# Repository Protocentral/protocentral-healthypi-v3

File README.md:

# ProtoCentral HealthyPi v3 HAT for Raspberry Pi

HealthyPi is the first fully open-source, full-featured vital sign monitor. Using the Raspberry Pi as its computing and display platform, the HealthyPi add-on HAT turns the Raspberry Pi into a vital sign monitoring system.

If you don't already have one, you can now buy HealthyPi from any of the following places:

* [Crowd Supply](https://www.crowdsupply.com/protocentral/healthypi-v3)
* [ProtoCentral India (Worldwide)](https://www.protocentral.com/open-source-health/1252-healthypi-v3-complete-kit-includes-raspberry-pi.html)
* [DigiKey](https://www.digikey.in/product-detail/en/crowd-supply-inc/CS-HEALTHYPI-01/1848-1035-ND)
* [Mouser](https://www.mouser.in/ProductDetail/392-CS-HEALTHYPI-01)

Repository Contents
-------------------
* **/firmware** - Atmel studio  and aduino example sketches.
* **/Hardware** - All Eagle design files (.brd, .sch)
* **/extras** - includes the datasheet
* **/gui** - HealthyPi GUI for Raspberry Pi and PC
* **/docs** - Documentation

Getting Started (On Raspberry Pi):
----------------------------------

### For getting started videos and tutorials, please go to [http://healthypi.protocentral.com](http://healthypi.protocentral.com)

Mount ProtoCentral's HealthyPi-v3 HAT carefully onto the Raspberry Pi Board's GPIO Pins. Connect this setup with the Raspberry Pi's Display or a HDMI Monitor. The HAT communicates with Raspberry Pi using UART interface on the GPIO pin header. Connect the ECG electrodes and SPO2 Probe to the ProtoCentral's Healthy PI Hat.

It's now easy to get started with our brand-new installation script. Just follow the following steps on your Raspberry Pi.

To start, open up the terminal window (Menu -> Accessories -> Terminal) on Raspbian running on your Raspberry Pi:

In the terminal window, type the following lines.

```bash
curl -sS http://pi.protocentral.com/hpi3.sh | sudo bash
```

It really is as simple as that !!

This code will install all the required overlays, configuration and application files to get the Healthy Pi up and running.

After the script reboots, you should be able to see the GUI display on the screen

### This completes the install!

If the above script does not work for you and would like to do a manual installation or would like to customize the code, check out [Advanced HealthyPi] (/docs/advanced-healthypi.md).

Using the HealthyPi GUI on Windows, MacOS and Linux
---------------------------------------------------
The HealthyPi board now streams the same data on the on-board USB port. This allows you to get the same data that goes to the Raspberry Pi, now on your desktop PC as well.

Java 8 is required on all platforms for running the processing-based GUI application. You can download Java for your platform from the following link.

[https://java.com/en/download/](https://java.com/en/download/)

#### Installing drivers (only for Windows)

HealthyPi uses the same drivers as an Arduino Zero. Once plugged in to the USB port, the device would be recognized as an "Unknown Device". You can locate the device is the Windows Device Manager and manually install the drivers provided in the "drivers" folder in the Windows Executable ZIP archive provided.

MacOS and Linux do not need any drivers to be installed.

### Processing GUI Installation

Download the zip file containing the executable files from the releases section for 32-bit/64-bit Windows. If you do not know if you have a 64-bit or 32-bit computer, please download the 32-bit version.

[Download the latest GUI for HealthyPi](https://github.com/Protocentral/protocentral-healthypi-v3/releases/latest)

Simply download the appropriate file for your operating system, unzip the contents and run the executable program contained in it.

### For more documentation, videos and tutorials, please go to [http://healthypi.protocentral.com](http://healthypi.protocentral.com)

License Information
===================

This product is open source! Both, our hardware and software are open source and licensed under the following licenses:

Hardware
---------

**All hardware is released under [Creative Commons Share-alike 4.0 International](http://creativecommons.org/licenses/by-sa/4.0/).**

You are free to:

* Share — copy and redistribute the material in any medium or format
* Adapt — remix, transform, and build upon the material for any purpose, even commercially.
The licensor cannot revoke these freedoms as long as you follow the license terms.

Under the following terms:

* Attribution — You must give appropriate credit, provide a link to the license, and indicate if changes were made. You may do so in any reasonable manner, but not in any way that suggests the licensor endorses you or your use.
* ShareAlike — If you remix, transform, or build upon the material, you must distribute your contributions under the same license as the original.

Software
--------

**All software is released under the MIT License(http://opensource.org/licenses/MIT).**

THE SOFTWARE IS PROVIDED "AS IS", WITHOUT WARRANTY OF ANY KIND, EXPRESS OR IMPLIED, INCLUDING BUT NOT LIMITED TO THE WARRANTIES OF MERCHANTABILITY, FITNESS FOR A PARTICULAR PURPOSE AND NONINFRINGEMENT. IN NO EVENT SHALL THE AUTHORS OR COPYRIGHT HOLDERS BE LIABLE FOR ANY CLAIM, DAMAGES OR OTHER LIABILITY, WHETHER IN AN ACTION OF CONTRACT, TORT OR OTHERWISE, ARISING FROM, OUT OF OR IN CONNECTION WITH THE SOFTWARE OR THE USE OR OTHER DEALINGS IN THE SOFTWARE.

Please check [*LICENSE.md*](LICENSE.md) for detailed license descriptions.

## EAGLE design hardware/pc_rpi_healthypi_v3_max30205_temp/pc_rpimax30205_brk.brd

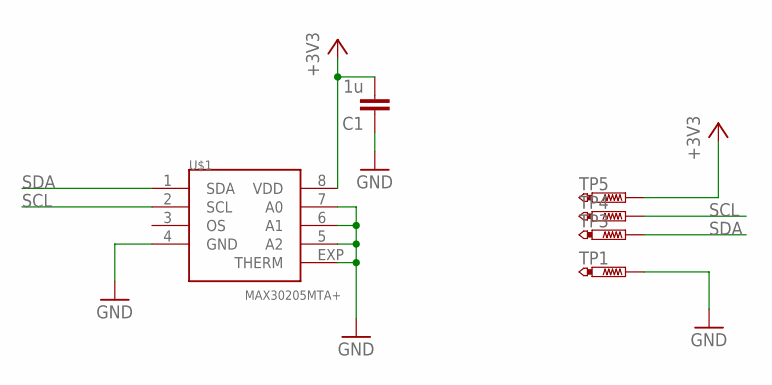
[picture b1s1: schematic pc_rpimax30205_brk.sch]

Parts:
C1: 1u; C0805
TP1, TP3, TP4, TP5: PTR1TP20SQ; TP20SQ
U$1: MAX30205MTA+; TDFN-08

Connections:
+3V3: C1.2, TP5.TP, U$1.8 (VDD)
GND: C1.1, TP1.TP, U$1.4 (GND), U$1.5 (A2), U$1.6 (A1), U$1.7 (A0), U$1.EXP (THERM)
SCL: TP4.TP, U$1.2 (SCL)
SDA: TP3.TP, U$1.1 (SDA)

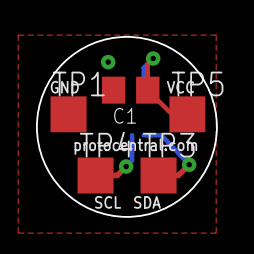
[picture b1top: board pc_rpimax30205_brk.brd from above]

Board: 4 copper layers, 10.0 x 10.0 mm, 6 parts (1 on the bottom side), 4 nets.

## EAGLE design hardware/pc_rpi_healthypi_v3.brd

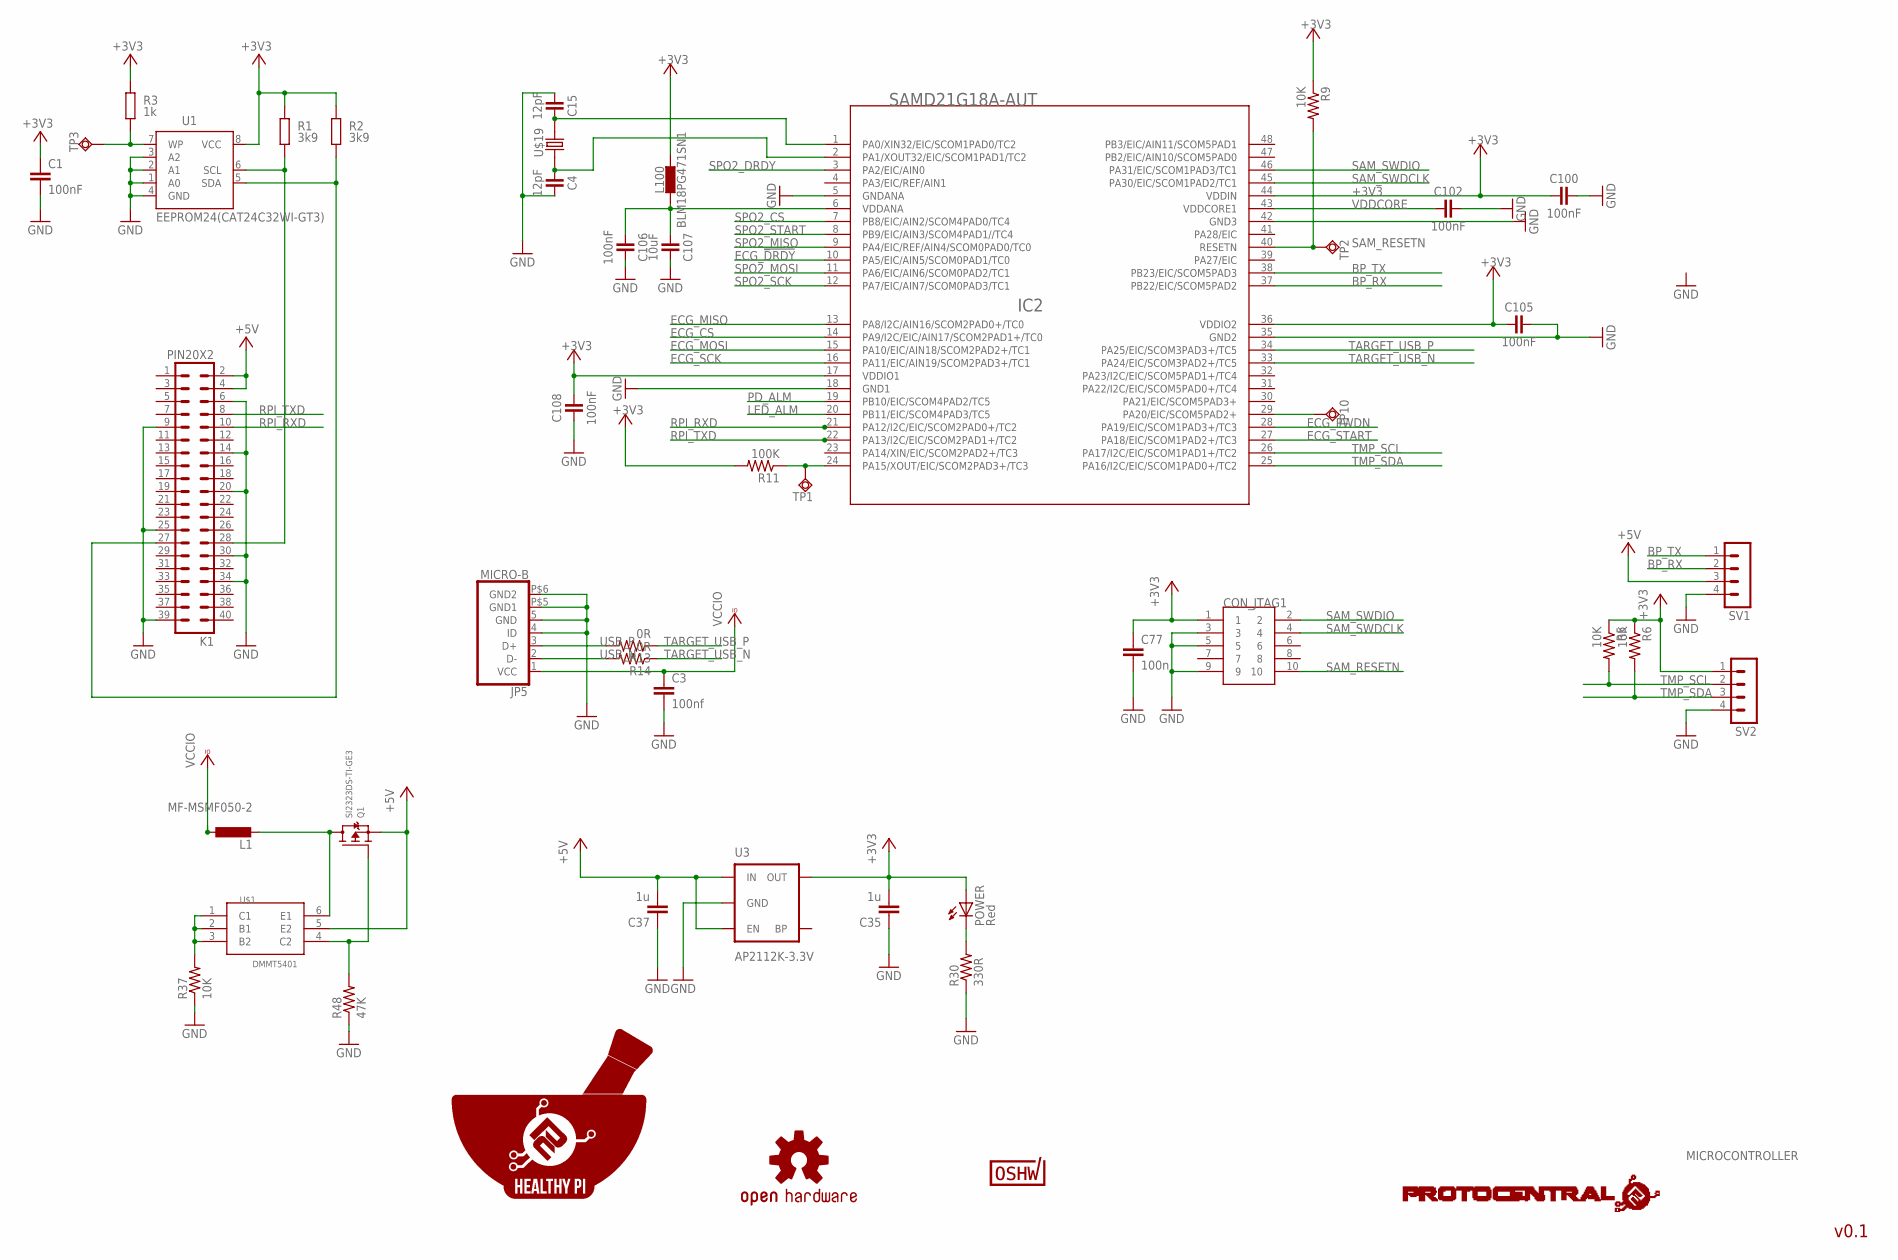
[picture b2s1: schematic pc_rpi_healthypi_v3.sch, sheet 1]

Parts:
C1: 100nF; C0805K
C3: 100nf; C0402
C4, C15: 12pF; C0402
C35, C37: 1u; C0402
C77: 100n; C0805
C100, C102, C105, C106, C108: 100nF; C0805
C107: 10uF; C0805
CON_JTAG1: HDR-SMT-50MIL/5X2(20021121-00010C4LF); HDR-SMT-50MIL/5X2
IC2: SAMD21G18A-AUT; TQFP48
JP5: MICRO-B
K1: PIN20X2; PIN_20X2
L1: MF-MSMF050-2; L1812
L100: BLM18PG471SN1; C0603
POWER: Red; CHIPLED_0603
Q1: SI2323DS-TI-GE3; SOT23-R
R1, R2: 3k9; M0805; TOLERANCE 5%
R3: 1k; M0805; TOLERANCE 5%
R5, R6: 10K; R0402
R9, R37: 10K; R0805
R11: 100K; R0805
R13, R14: 0R; R0402
R30: 330R; R0402
R48: 47K; R0805
SV1, SV2: MA04-1
TP1, TP2, TP3, TP10: TPSQB1,27; B1,27
U1: EEPROM24(CAT24C32WI-GT3); SOIC8
U3: AP2112K-3.3V; SOT23-5
U$1: DMMT5401; SOT26
U$5: OSHW-LOGOM; OSHW-LOGO-M
U$6: PROTY_LOGO_WITH_TEXT; PROTY_WITH_TEXT
U$13: CERT-SMALL; CERT-SMALL-SILK
U$15: HEALTHYPI
U$19: 520-327-12.5-34B(32.768KHZ); ECX-31B

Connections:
+3V3: C1.1, C35.2, C77.1, C100.1, C105.1, C108.2, CON_JTAG1.1, IC2.17 (VDDIO1), IC2.36 (VDDIO2), IC2.44 (VDDIN), L100.2, POWER.A, R1.2, R2.2, R3.2, R5.1, R6.1, R9.1, R11.2, SV2.1, U1.8 (VCC), U3.5 (OUT); also elsewhere on the board
+5V: C37.2, K1.2, K1.4, Q1.2 (S), SV1.3, U3.1 (IN), U3.3 (EN), U$1.5 (E2)
BP_RX: IC2.37 (PB22/EIC/SCOM5PAD2), SV1.2
BP_TX: IC2.38 (PB23/EIC/SCOM5PAD3), SV1.1
ECG_!DRDY: IC2.10 (PA5/EIC/AIN5/SCOM0PAD1/TC0); also elsewhere on the board
ECG_CS: IC2.14 (PA9/I2C/EIC/AIN17/SCOM2PAD1+/TC0); also elsewhere on the board
ECG_MISO: IC2.13 (PA8/I2C/AIN16/SCOM2PAD0+/TC0); also elsewhere on the board
ECG_MOSI: IC2.15 (PA10/EIC/AIN18/SCOM2PAD2+/TC1); also elsewhere on the board
ECG_PWDN: IC2.28 (PA19/EIC/SCOM1PAD3+/TC3); also elsewhere on the board
ECG_SCK: IC2.16 (PA11/EIC/AIN19/SCOM2PAD3+/TC1); also elsewhere on the board
ECG_START: IC2.27 (PA18/EIC/SCOM1PAD2+/TC3); also elsewhere on the board
GND: C1.2, C3.2, C4.2, C15.1, C35.1, C37.1, C77.2, C100.2, C102.2, C105.2, C106.2, C107.2, C108.1, CON_JTAG1.3, CON_JTAG1.5, CON_JTAG1.9, IC2.5 (GNDANA), IC2.18 (GND1), IC2.35 (GND2), IC2.42 (GND3), JP5.4 (ID), JP5.5 (GND), JP5.P$5 (GND1), JP5.P$6 (GND2), K1.6, K1.9, K1.14, K1.20, K1.25, K1.30, K1.34, K1.39, R30.1, R37.1, R48.1, SV1.4, SV2.4, U1.1 (A0), U1.2 (A1), U1.3 (A2), U1.4 (GND), U3.2 (GND); also elsewhere on the board
LED_ALM: IC2.20 (PB11/EIC/SCOM4PAD3/TC5); also elsewhere on the board
unnamed: K1.28, R1.1, U1.6 (SCL)
unnamed: K1.27, R2.1, U1.5 (SDA)
unnamed: R3.1, TP3.TP, U1.7 (WP)
unnamed: C15.2, IC2.1 (PA0/XIN32/EIC/SCOM1PAD0/TC2), U$19.P$2 (2)
unnamed: C106.1, C107.1, IC2.6 (VDDANA), L100.1
unnamed: POWER.C, R30.2
unnamed: C4.1, IC2.2 (PA1/XOUT32/EIC/SCOM1PAD1/TC2), U$19.P$1 (1)
unnamed: IC2.24 (PA15/XOUT/EIC/SCOM2PAD3+/TC3), R11.1, TP1.TP
unnamed: IC2.29 (PA20/EIC/SCOM5PAD2+), TP10.TP
unnamed: R37.2, U$1.1 (C1), U$1.2 (B1), U$1.3 (B2)
unnamed: Q1.1 (G), R48.2, U$1.4 (C2)
unnamed: L1.2, Q1.3 (D), U$1.6 (E1)
PD_ALM: IC2.19 (PB10/EIC/SCOM4PAD2/TC5); also elsewhere on the board
RPI_RXD: IC2.21 (PA12/I2C/EIC/SCOM2PAD0+/TC2), K1.10
RPI_TXD: IC2.22 (PA13/I2C/EIC/SCOM2PAD1+/TC2), K1.8
SAM_RESETN: CON_JTAG1.10, IC2.40 (RESETN), R9.2, TP2.TP
SAM_SWDCLK: CON_JTAG1.4, IC2.45 (PA30/EIC/SCOM1PAD2/TC1)
SAM_SWDIO: CON_JTAG1.2, IC2.46 (PA31/EIC/SCOM1PAD3/TC1)
SPO2_CS: IC2.7 (PB8/EIC/AIN2/SCOM4PAD0/TC4); also elsewhere on the board
SPO2_DRDY: IC2.3 (PA2/EIC/AIN0); also elsewhere on the board
SPO2_MISO: IC2.9 (PA4/EIC/REF/AIN4/SCOM0PAD0/TC0); also elsewhere on the board
SPO2_MOSI: IC2.11 (PA6/EIC/AIN6/SCOM0PAD2/TC1); also elsewhere on the board
SPO2_SCK: IC2.12 (PA7/EIC/AIN7/SCOM0PAD3/TC1); also elsewhere on the board
SPO2_START: IC2.8 (PB9/EIC/AIN3/SCOM4PAD1//TC4); also elsewhere on the board
TARGET_USB_N: IC2.33 (PA24/EIC/SCOM3PAD2+/TC5), R14.1
TARGET_USB_P: IC2.34 (PA25/EIC/SCOM3PAD3+/TC5), R13.1
TMP_SCL: IC2.26 (PA17/I2C/EIC/SCOM1PAD1+/TC2), R5.2, SV2.2
TMP_SDA: IC2.25 (PA16/I2C/EIC/SCOM1PAD0+/TC2), R6.2, SV2.3
USB_N: JP5.2 (D-), R14.2
USB_P: JP5.3 (D+), R13.2
VCCIO: C3.1, JP5.1 (VCC), L1.1
VDDCORE: C102.1, IC2.43 (VDDCORE1)

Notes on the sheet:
v0.1
MICROCONTROLLER

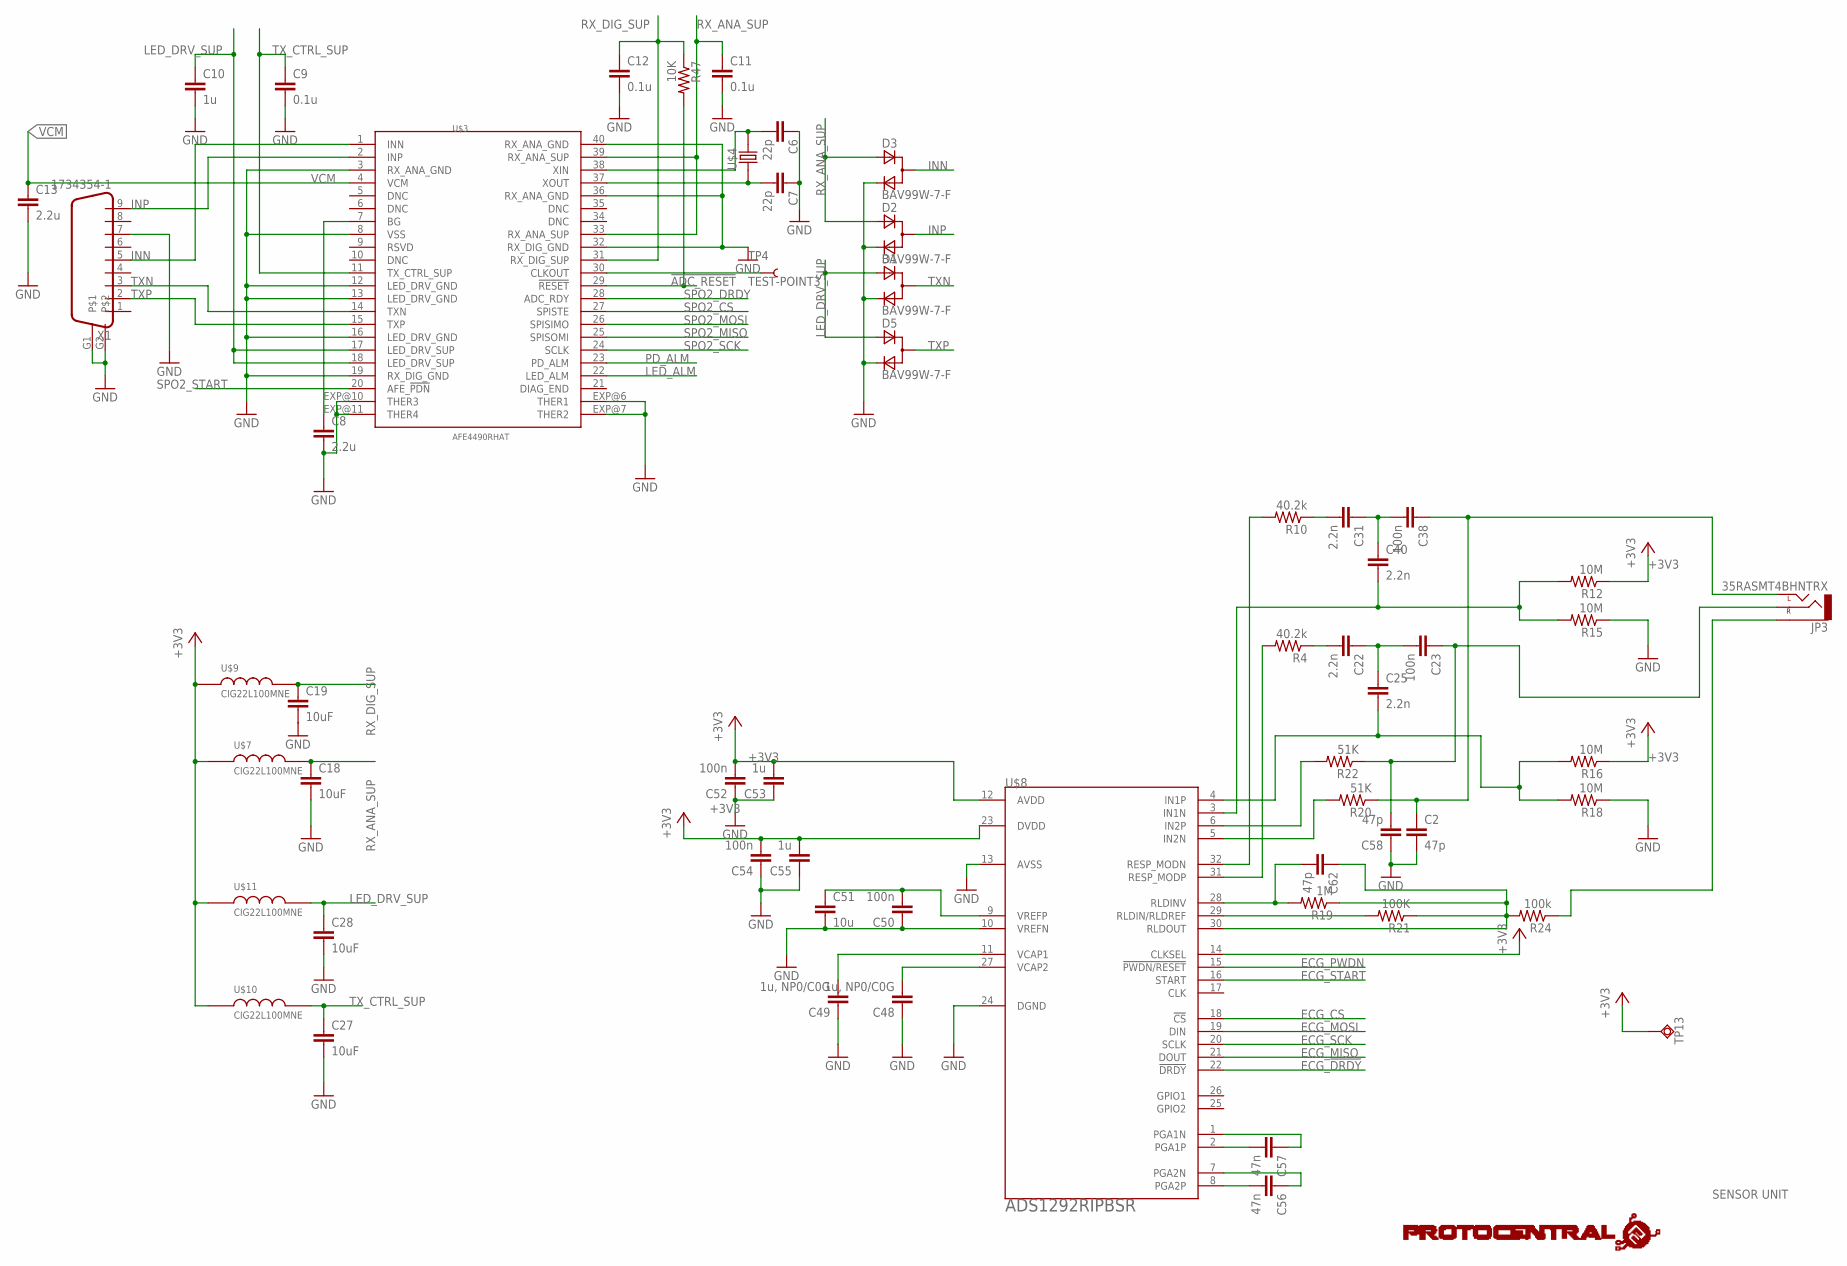
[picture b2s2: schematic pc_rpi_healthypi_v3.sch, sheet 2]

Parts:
C2, C58, C62: 47p; C0402
C6, C7: 22p; C0402
C8, C13: 2.2u; C0402
C9, C11, C12: 0.1u; C0402
C10: 1u; C0805
C18, C19, C27, C28: 10uF; C0805
C22, C25, C31, C40: 2.2n; C0402
C23, C38, C50, C52, C54: 100n; C0402
C48, C49: 1u, NP0/C0G; C0402
C51: 10u; C0603
C53, C55: 1u; C0402
C56, C57: 47n; C0402
D1, D2, D3, D5: BAV99W-7-F; SOT323
JP3: 35RASMT4BHNTRX; AUDIO-JACK-3.5MM-SMD
R4, R10: 40.2k; R0402
R12, R15, R16, R18: 10M; R0402
R19: 1M; R0402
R20, R22: 51K; R0402
R21: 100K; R0402
R24: 100k; R0402
R47: 10K; R0402
TP4: TEST-POINT3; PAD.03X.03
TP13: TPSQB1,27; B1,27
U$2: PROTY_LOGO_WITH_TEXT; PROTY_WITH_TEXT
U$3: AFE4490RHAT; QFN-40
U$4: ABM3
U$7, U$9, U$10, U$11: CIG22L100MNE; LPS
U$8: ADS1292RIPBSR; SQFP-S-5X5-32
X1: 1734354-1; DB9-STRIGHT

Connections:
!ADC_RESET: R47.2, U$3.29 (!RESET)
+3V3: C52.2, C53.2, C54.2, C55.2, R12.1, R16.1, TP13.TP, U$7.1, U$8.12 (AVDD), U$8.14 (CLKSEL), U$8.23 (DVDD), U$9.1, U$10.1, U$11.1; also elsewhere on the board
ECG_!DRDY: U$8.22 (!DRDY); also elsewhere on the board
ECG_CS: U$8.18 (!CS); also elsewhere on the board
ECG_MISO: U$8.21 (DOUT); also elsewhere on the board
ECG_MOSI: U$8.19 (DIN); also elsewhere on the board
ECG_PWDN: U$8.15 (!PWDN/RESET); also elsewhere on the board
ECG_SCK: U$8.20 (SCLK); also elsewhere on the board
ECG_START: U$8.16 (START); also elsewhere on the board
GND: C2.2, C6.1, C7.1, C8.2, C9.2, C10.2, C11.2, C12.2, C13.2, C18.2, C19.2, C27.2, C28.2, C48.1, C49.1, C50.1, C51.2, C52.1, C53.1, C54.1, C55.1, C58.1, D1.2 (C), D2.2 (C), D3.2 (C), D5.2 (C), R15.1, R18.1, U$3.3 (RX_ANA_GND), U$3.8 (VSS), U$3.12 (LED_DRV_GND), U$3.13 (LED_DRV_GND), U$3.16 (LED_DRV_GND), U$3.19 (RX_DIG_GND), U$3.32 (RX_DIG_GND), U$3.36 (RX_ANA_GND), U$3.40 (RX_ANA_GND), U$3.EXP@6 (THER1), U$3.EXP@7 (THER2), U$3.EXP@10 (THER3), U$3.EXP@11 (THER4), U$8.10 (VREFN), U$8.13 (AVSS), U$8.24 (DGND), X1.7, X1.G1, X1.G2; also elsewhere on the board
INN: D3.1 (CA), U$3.1 (INN), X1.5
INP: D2.1 (CA), U$3.2 (INP), X1.9
LED_ALM: U$3.22 (LED_ALM); also elsewhere on the board
LED_DRV_SUP: C10.1, C28.1, D1.3 (A), D5.3 (A), U$3.17 (LED_DRV_SUP), U$3.18 (LED_DRV_SUP), U$11.2
unnamed: R4.2, U$8.31 (RESP_MODP)
unnamed: C6.2, U$3.38 (XIN), U$4.2
unnamed: C22.2, R4.1
unnamed: C22.1, C23.2, C25.1
unnamed: R22.2, U$8.6 (IN2P)
unnamed: C7.2, U$3.37 (XOUT), U$4.1
unnamed: R20.2, U$8.5 (IN2N)
unnamed: C8.1, U$3.7 (BG)
unnamed: TP4.P$1, U$3.30 (CLKOUT)
unnamed: C48.2, U$8.27 (VCAP2)
unnamed: R10.2, U$8.32 (RESP_MODN)
unnamed: C31.2, R10.1
unnamed: C31.1, C38.2, C40.1
unnamed: C2.1, C38.1, JP3.TIP (LEFT), R20.1
unnamed: C40.2, R12.2, R15.2, U$8.3 (IN1N)
unnamed: C25.2, R16.2, R18.2, U$8.4 (IN1P)
unnamed: R21.2, U$8.29 (RLDIN/RLDREF)
unnamed: C62.2, R19.2, U$8.28 (RLDINV)
unnamed: C49.2, U$8.11 (VCAP1)
unnamed: C56.2, U$8.8 (PGA2P)
unnamed: C56.1, U$8.7 (PGA2N)
unnamed: C50.2, C51.1, U$8.9 (VREFP)
unnamed: C57.2, U$8.2 (PGA1P)
unnamed: C57.1, U$8.1 (PGA1N)
unnamed: C23.1, C58.2, JP3.RING (RIGHT), R22.1
unnamed: C62.1, R19.1, R21.1, R24.2, U$8.30 (RLDOUT)
unnamed: JP3.SLEEVE, R24.1
PD_ALM: U$3.23 (PD_ALM); also elsewhere on the board
RX_ANA_SUP: C11.1, C18.1, D2.3 (A), D3.3 (A), U$3.33 (RX_ANA_SUP), U$3.39 (RX_ANA_SUP), U$7.2
RX_DIG_SUP: C12.1, C19.1, R47.1, U$3.31 (RX_DIG_SUP), U$9.2
SPO2_CS: U$3.27 (SPISTE); also elsewhere on the board
SPO2_DRDY: U$3.28 (ADC_RDY); also elsewhere on the board
SPO2_MISO: U$3.25 (SPISOMI); also elsewhere on the board
SPO2_MOSI: U$3.26 (SPISIMO); also elsewhere on the board
SPO2_SCK: U$3.24 (SCLK); also elsewhere on the board
SPO2_START: U$3.20 (AFE_!PDN); also elsewhere on the board
TXN: D1.1 (CA), U$3.14 (TXN), X1.3
TXP: D5.1 (CA), U$3.15 (TXP), X1.2
TX_CTRL_SUP: C9.1, C27.1, U$3.11 (TX_CTRL_SUP), U$10.2
VCM: C13.1, U$3.4 (VCM)

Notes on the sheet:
SENSOR UNIT

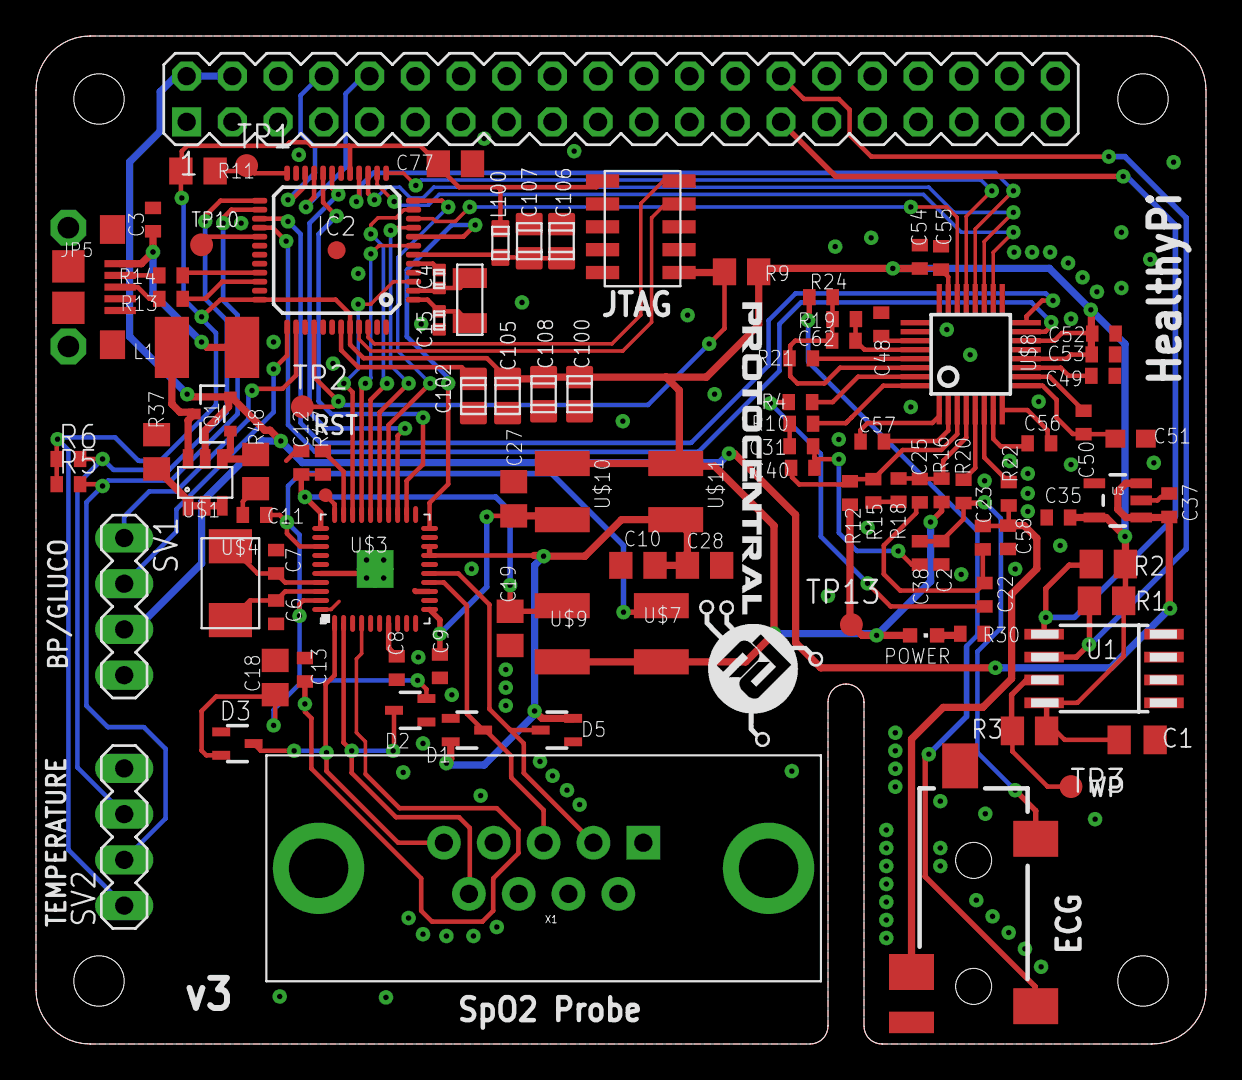
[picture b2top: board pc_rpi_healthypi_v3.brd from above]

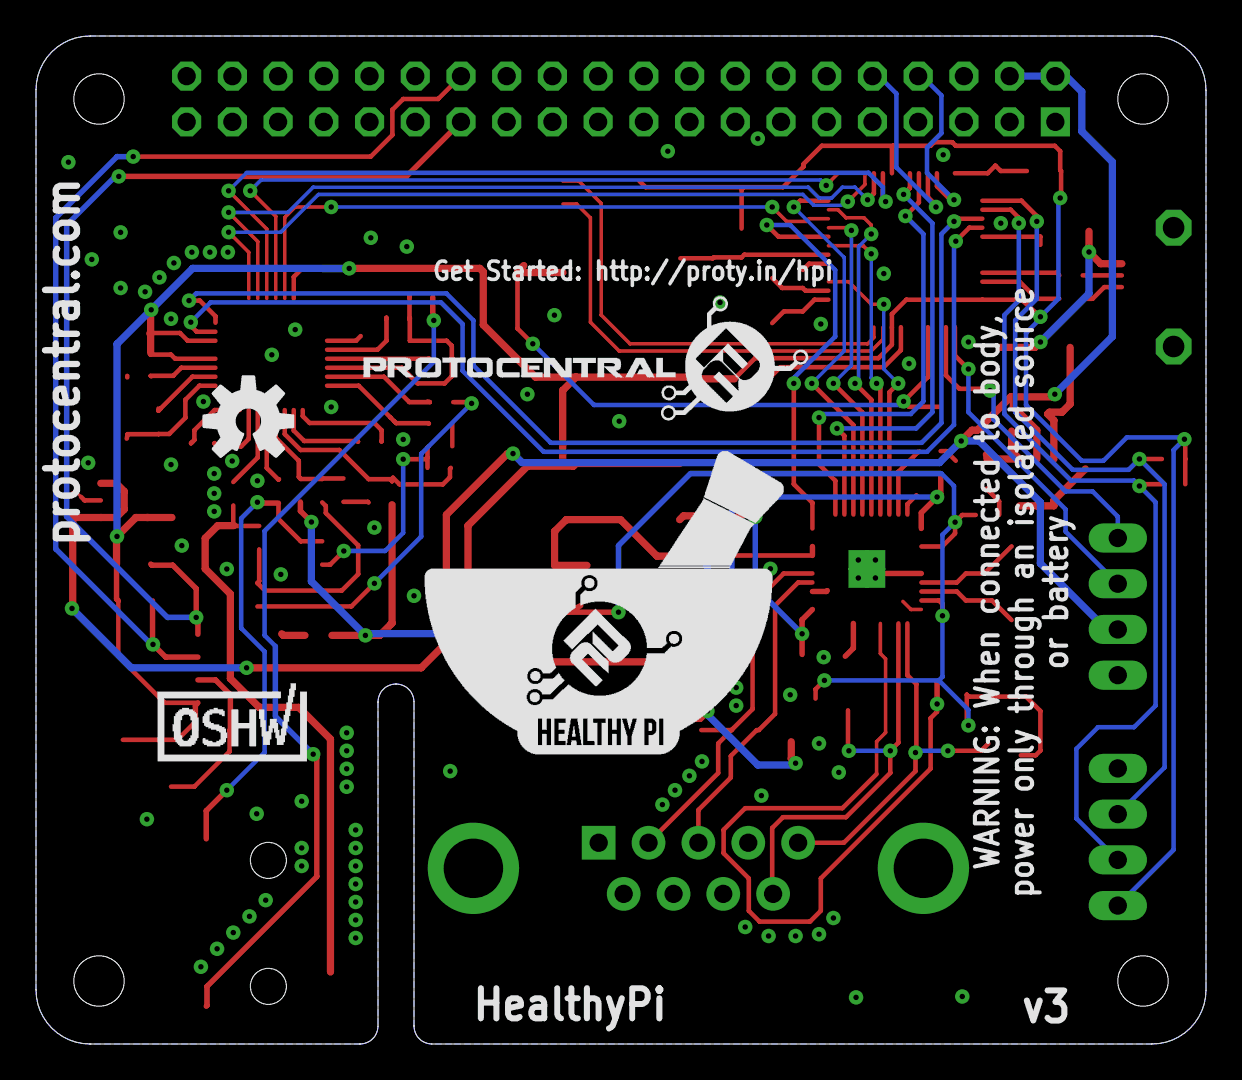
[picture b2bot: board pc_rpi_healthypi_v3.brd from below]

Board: 4 copper layers, 65.0 x 56.0 mm, 106 parts (4 on the bottom side), 82 nets.

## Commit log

2017-05-06 Init commit
2017-05-11 New GUI changes
2017-05-27 updated arduino code for v3
    included max30205 temperature sensor
2017-05-28 Added MQTT support for processing application
2017-06-01 Updated Arduino main firmware
2017-07-14 Set theme jekyll-theme-slate
2017-07-14 Create CNAME
2017-07-14 Added .gitignore
2017-07-14 Added docs
2017-07-14 Updated docs main board image
2017-07-14 Set theme jekyll-theme-leap-day
2017-07-14 Added screen capture
2017-07-14 Minor error fixes
2017-07-14 Added new images and edited docs
2017-07-14 Updated docs index
2017-07-14 Updated docs
2017-07-16 Updated HealthyPi documentation
2017-07-16 Set theme jekyll-theme-minimal
2017-07-16 Update docs
2017-07-16 Added embedded video
2017-07-16 Added assembly videos for complete kit and USB standalone
2017-07-19 Updated new file structure
2017-07-19 Commit HealthyPi v1.0
2017-07-19 Removed unwanted images
2017-07-20 Updated GUI app for selecting serial ports
2017-07-20 Updated index.md, Fixed broken links
2017-07-20 Updated Index.md
2017-07-20 Updated releases link in docs
2017-08-02 Changed yml config
2017-08-02 Updated config.yml
2017-08-02 Added new firmware
    Bug fixes in heart rate and respiration rate algorithm
2017-08-02 Added new release files, documentation about firmware upgrades.
2017-08-03 Corrected afe44xx naming, removed header file
2017-10-21 Added temperature sensor board schematics
2018-02-03 Create new v2.0 with MQTT support
2018-02-04 Updated GUI layout for PI screen
2018-02-04 Updated MQTT Code, minor code cleanup
2018-02-04 Corrected MQTT feed data
2018-03-10 Updated docs to include purchase links
2018-03-11 Update docs index
2018-04-08 Updated docs to include packet format
2018-04-10 Added Jekyll theme for docs
2018-04-10 Minor update to docs
2018-08-14 Added GUI with color backgrounds shown an Defcon
2018-12-24 Create Frequently asked questions
2018-12-24 Rename Frequently asked questions to Frequently asked questions.md
2018-12-26 Rename docs/Frequently asked questions.md to FAQ
2018-12-26 Rename FAQ to FAQ.md
2020-02-18 Update CNAME
2024-12-11 Updated docs/jekyll-docs-theme.gemspec

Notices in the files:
README.md:
CC-BY-SA-4.0
parts and their libraries:
SparkFun-Connectors: Licensing: Creative Commons ShareAlike 4.0 International - https://creativecommons.org/licenses/by-sa/4.0
